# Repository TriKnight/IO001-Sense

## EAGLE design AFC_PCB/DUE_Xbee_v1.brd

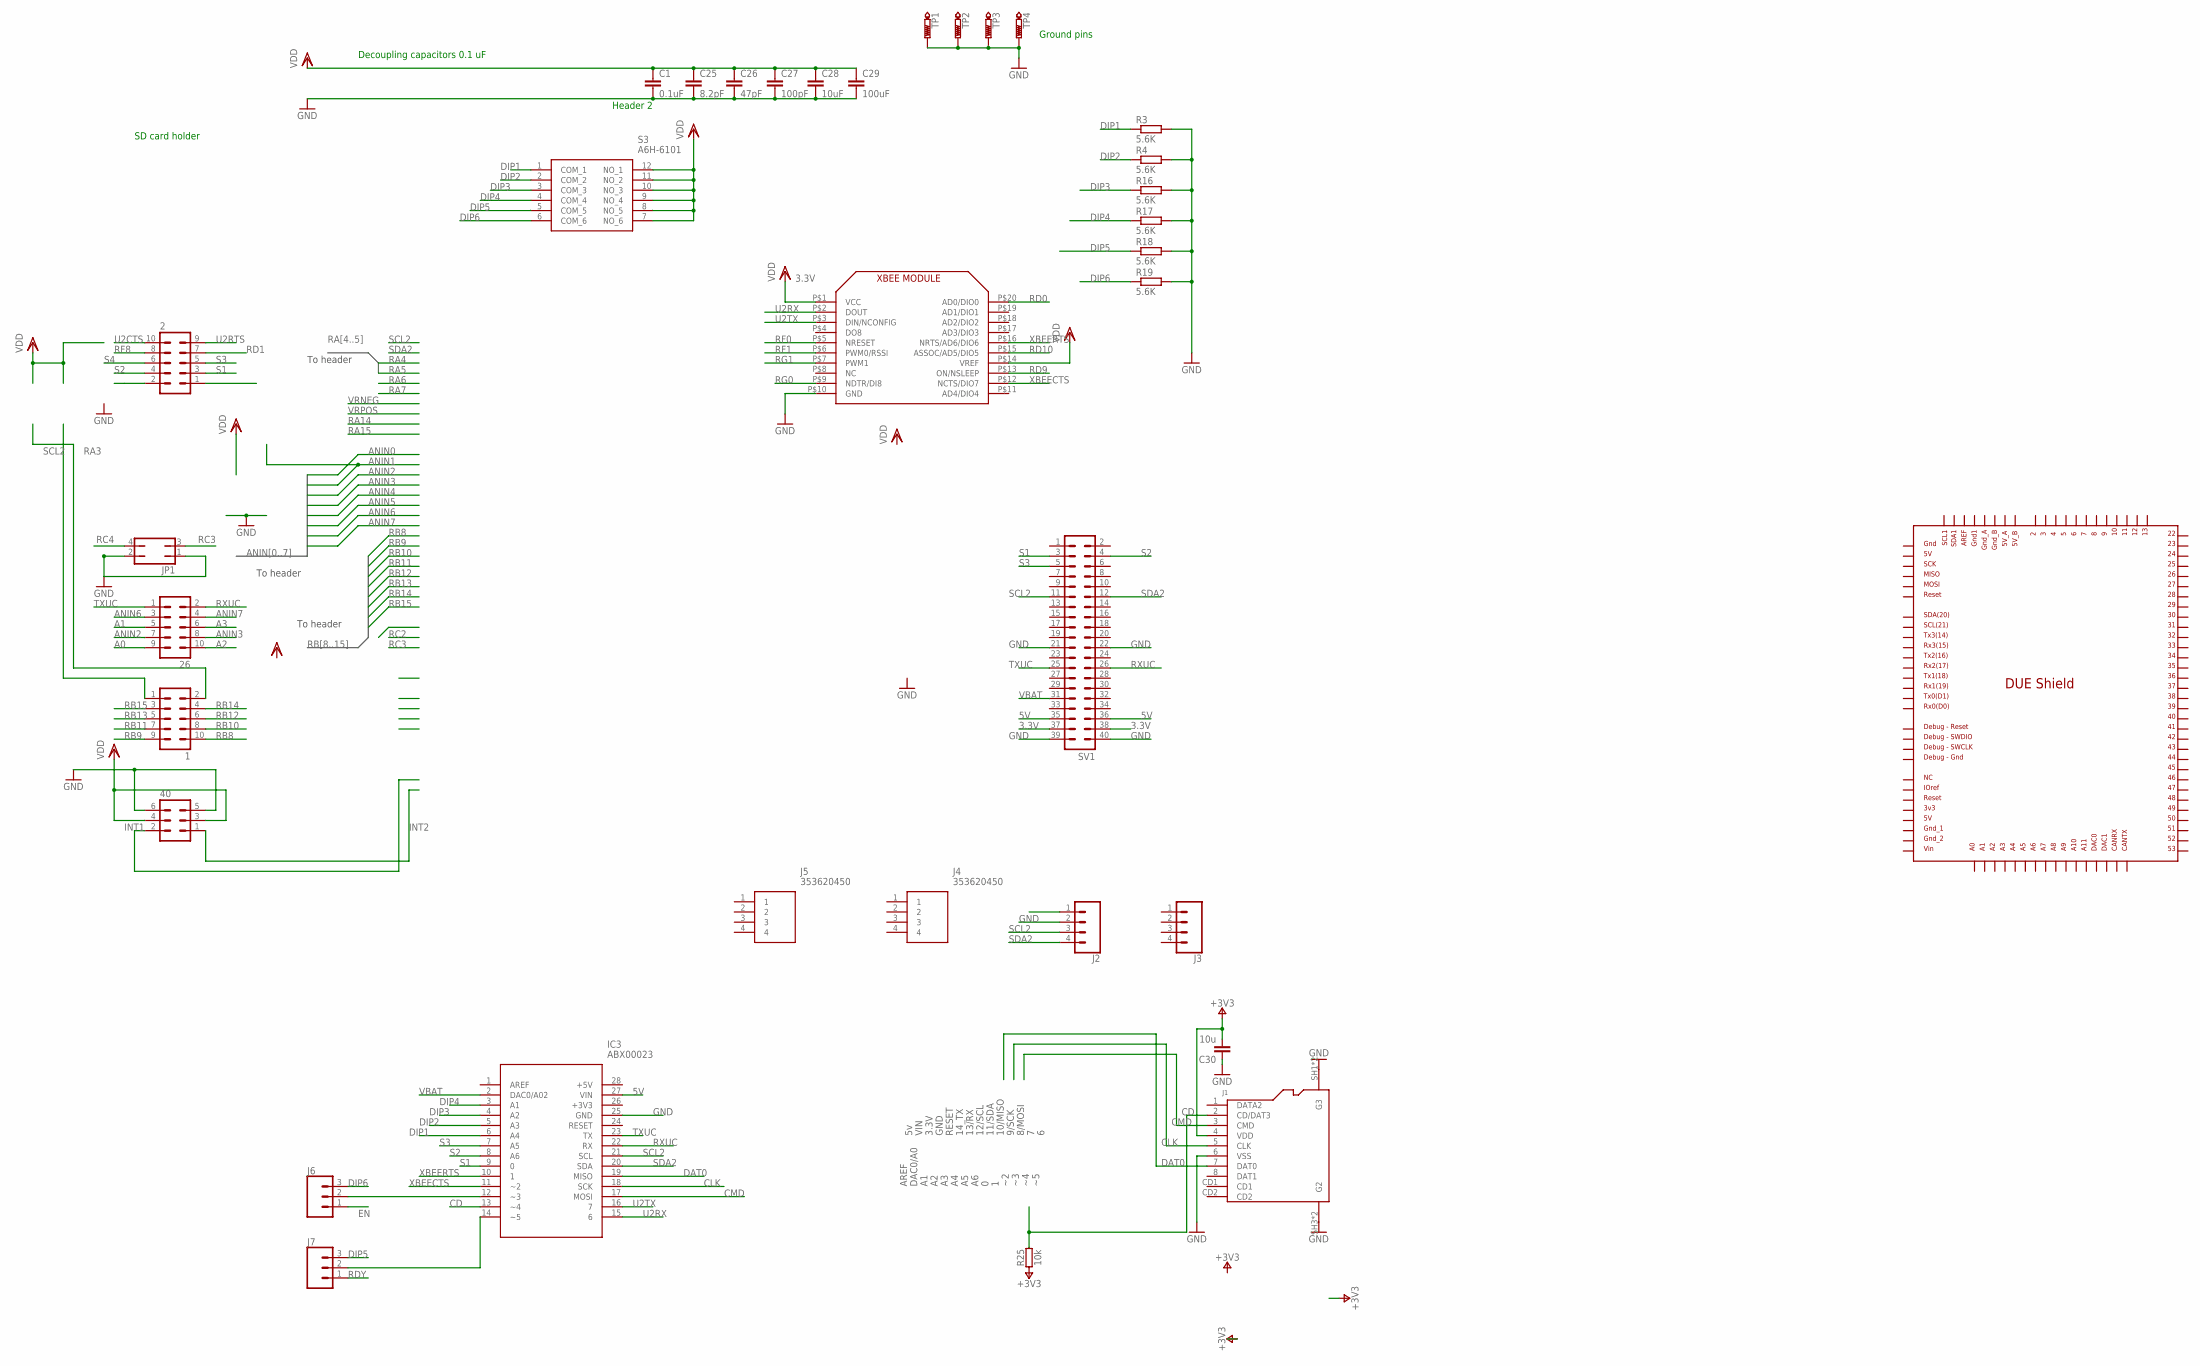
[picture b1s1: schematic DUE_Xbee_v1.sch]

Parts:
1, 2, 26: MA05-2
40: MA03-2
C1: 0.1uF; C0805K
C25: 8.2pF; C0805K
C26: 47pF; C0805K
C27: 100pF; C0805K
C28: 10uF; C0805K
C29: 100uF; C0805K
C30: 10u; 0805-R2013X50N
IC3: ABX00023
J1: AMPHENOL_114-00841-68
J2, J3: CONN_04POLAR_LOCK; MOLEX-1X4_LOCK
J4, J5: 353620450; SHDR4W50P0X200_1X4_1030X550X85
J6, J7: CONN_03LOCK; 1X03_LOCK
JP1: JP2Q
R3, R4, R16, R17, R18, R19: 5.6K; R0805
R25: 10k; 0805-R2013X50N
S3: A6H-6101; A6H6101
SV1: ML40
TP1, TP2, TP3, TP4: PTR1PAD1-13; P1-13
U$1: XBEE
U$2: DUE(NORMAL)

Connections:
3.3V: 40.3, 40.4, C1.1, C25.1, C26.1, C27.1, C28.1, C29.1, J2.1, S3.7 (NO_6), S3.8 (NO_5), S3.9 (NO_4), S3.10 (NO_3), S3.11 (NO_2), S3.12 (NO_1), SV1.37, SV1.38, U$1.P$1 (VCC), U$1.P$14 (VREF)
5V: IC3.27 (VIN), SV1.35, SV1.36
+3V3: C30.2, J1.4 (VDD), R25.1
A0: 26.9
A1: 26.5
A2: 26.10
A3: 26.6
ANIN2: 26.7
ANIN3: 26.8
ANIN6: 26.3
ANIN7: 26.4
CD: IC3.13 (~4), J1.2 (CD/DAT3), R25.2
CLK: IC3.18 (SCK), J1.5 (CLK)
CMD: IC3.17 (MOSI), J1.3 (CMD)
DAT0: IC3.19 (MISO), J1.7 (DAT0)
DIP1: IC3.6 (A4), R3.1, S3.1 (COM_1)
DIP2: IC3.5 (A3), R4.1, S3.2 (COM_2)
DIP3: IC3.4 (A2), R16.1, S3.3 (COM_3)
DIP4: IC3.3 (A1), R17.1, S3.4 (COM_4)
DIP5: J7.3, R18.1, S3.5 (COM_5)
DIP6: J6.3, R19.1, S3.6 (COM_6)
EN: J6.1
GND: 40.5, 40.6, C1.2, C25.2, C26.2, C27.2, C28.2, C29.2, C30.1, IC3.25 (GND), J1.6 (VSS), J1.SH1 (G3), J1.SH2 (G3), J1.SH3 (G2), J1.SH4 (G2), J2.2, JP1.1, JP1.2, R3.2, R4.2, R16.2, R17.2, R18.2, R19.2, SV1.21, SV1.22, SV1.39, SV1.40, TP1.1, TP2.1, TP3.1, TP4.1, U$1.P$10 (GND)
INT1: 40.2
INT2: 40.1
unnamed: IC3.12 (~3), J6.2
unnamed: IC3.14 (~5), J7.2
RA3: 1.2
RB8: 1.10
RB9: 1.9
RB10: 1.8
RB11: 1.7
RB12: 1.6
RB13: 1.5
RB14: 1.4
RB15: 1.3
RC3: JP1.3
RC4: JP1.4
RD0: U$1.P$20 (AD0/DIO0)
RD1: 2.7
RD9: U$1.P$13 (ON/NSLEEP)
RD10: U$1.P$15 (ASSOC/AD5/DIO5)
RDY: J7.1
RF0: U$1.P$5 (NRESET)
RF1: U$1.P$6 (PWM0/RSSI)
RF8: 2.8
RG0: U$1.P$9 (NDTR/DI8)
RG1: U$1.P$7 (PWM1)
RXUC: 26.2, IC3.22 (RX), SV1.26
S1: 2.3, IC3.9 (0), SV1.3
S2: 2.4, IC3.8 (A6), SV1.4
S3: 2.5, IC3.7 (A5), SV1.5
S4: 2.6
SCL2: 1.1, IC3.21 (SCL), J2.3, SV1.11
SDA2: IC3.20 (SDA), J2.4, SV1.12
TXUC: 26.1, IC3.23 (TX), SV1.25
U2CTS: 2.10
U2RTS: 2.9
U2RX: IC3.15 (6), U$1.P$2 (DOUT)
U2TX: IC3.16 (7), U$1.P$3 (DIN/NCONFIG)
VBAT: IC3.2 (DAC0/A02), SV1.31
XBEECTS: IC3.11 (~2), U$1.P$12 (NCTS/DIO7)
XBEERTS: IC3.10 (1), U$1.P$16 (NRTS/AD6/DIO6)

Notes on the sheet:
To header
SD card holder
Decoupling capacitors 0.1 uF
Header 2
Ground pins
AREF
DAC0/A0
8/MOSI
9/SCK
10/MISO
11/SDA
12/SCL
13/RX
14_TX
RESET
GND
3.3V
VIN

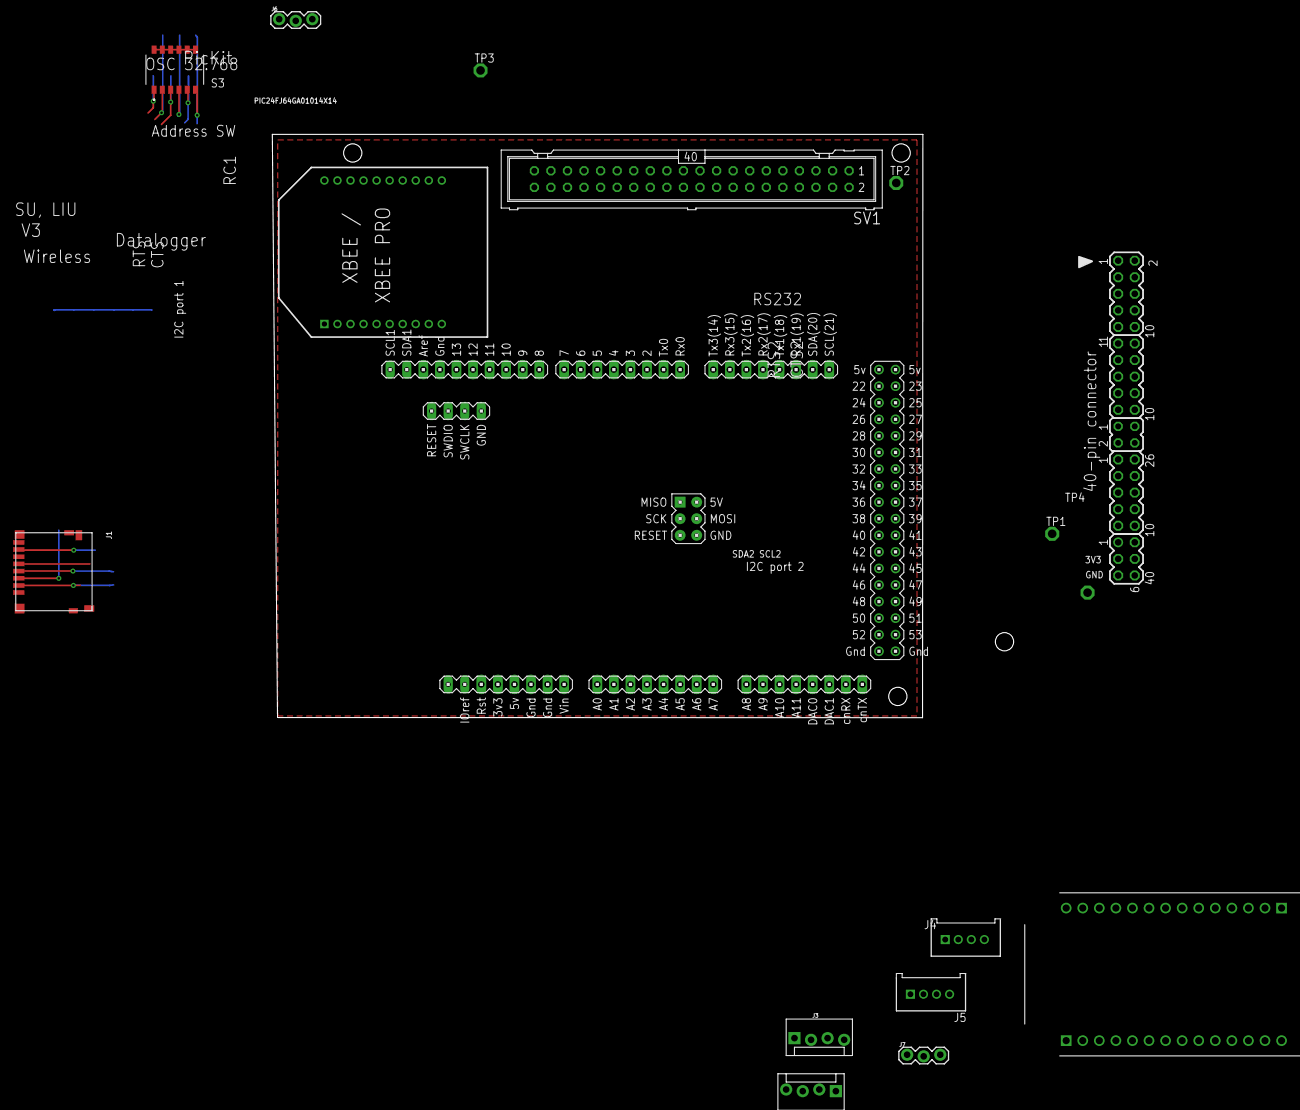
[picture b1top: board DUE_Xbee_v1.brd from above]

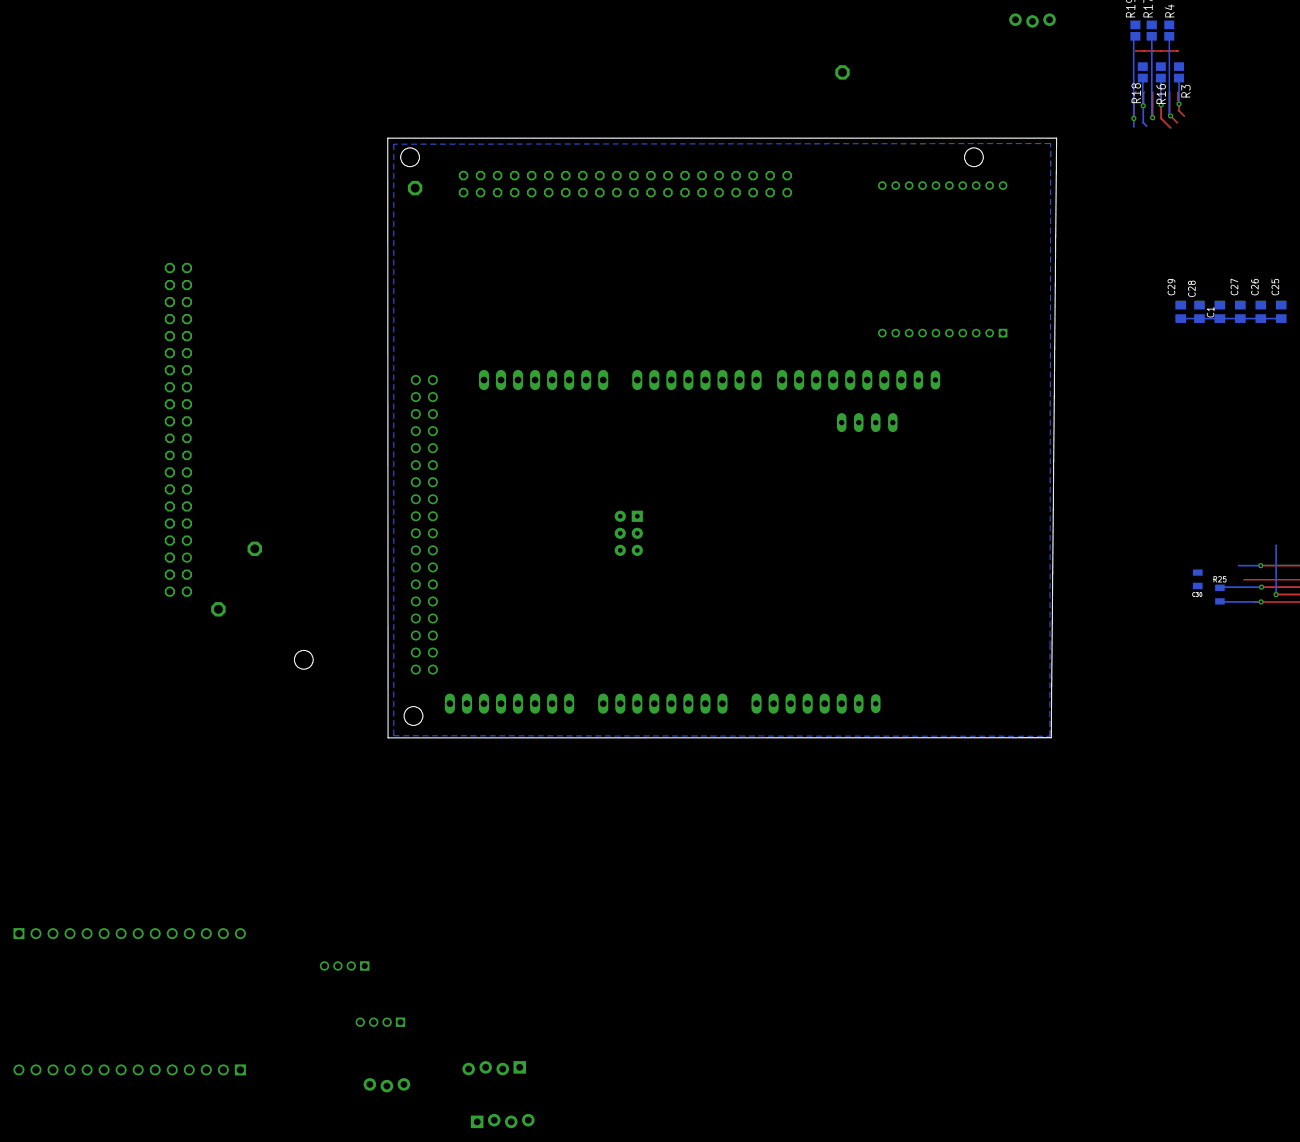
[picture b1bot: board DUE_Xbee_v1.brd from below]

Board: 2 copper layers, 99.7 x 89.4 mm, 35 parts (14 on the bottom side), 28 nets.

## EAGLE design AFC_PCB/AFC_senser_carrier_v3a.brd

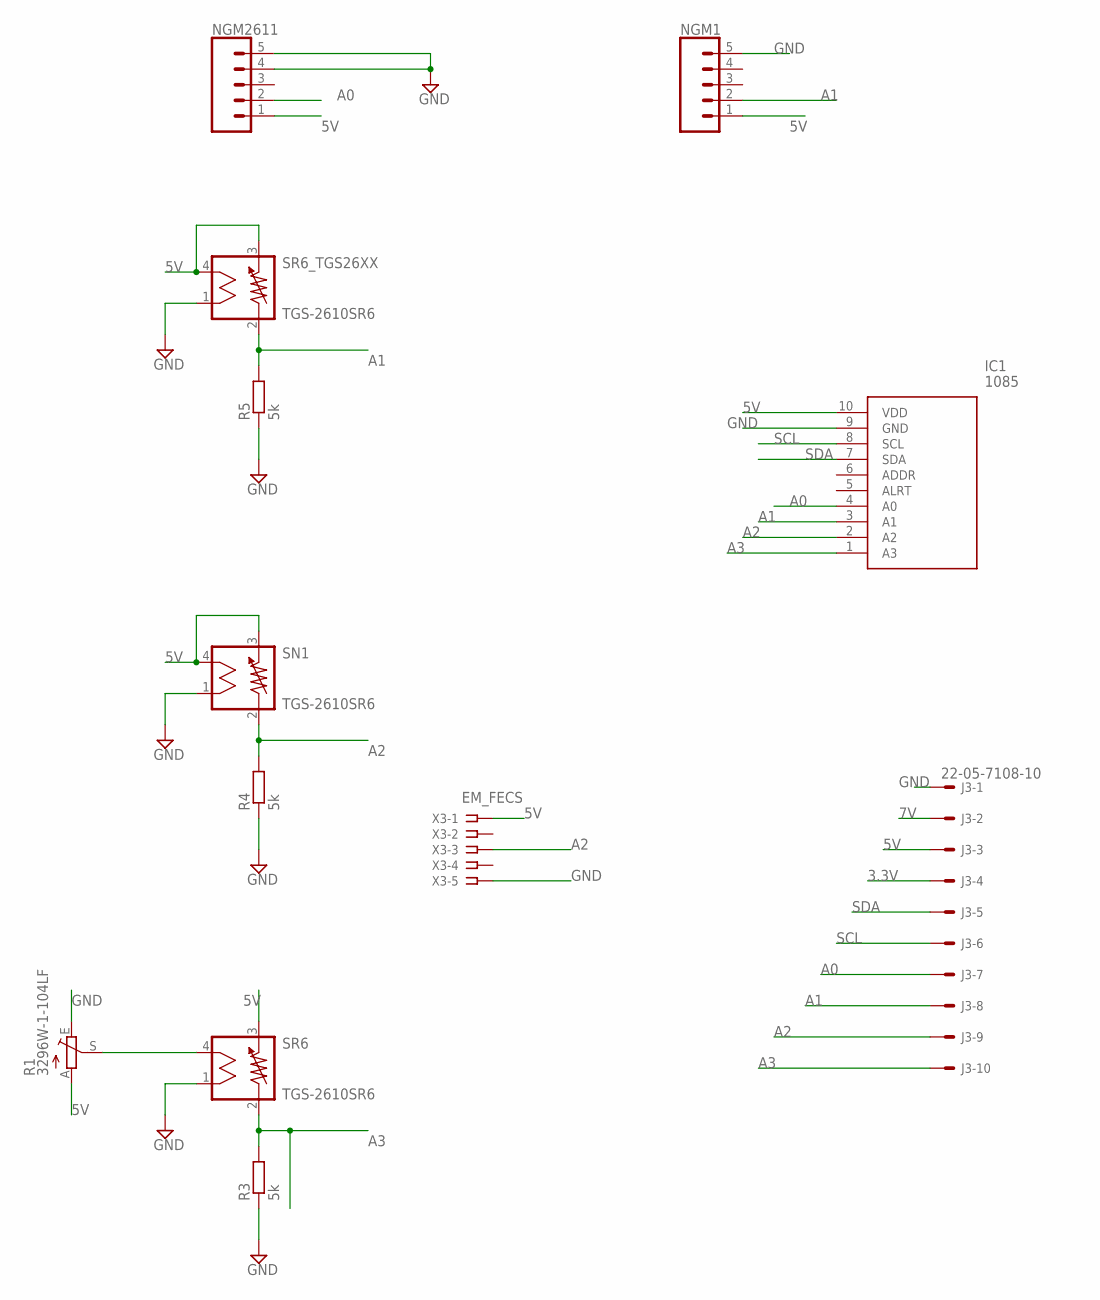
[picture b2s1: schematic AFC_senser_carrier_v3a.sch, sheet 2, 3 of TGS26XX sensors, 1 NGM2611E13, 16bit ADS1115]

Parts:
IC1: 1085
J3: 22-05-7108-10; 7395-10
NGM1, NGM2611: CONN_05LOCK; 1X05_LOCK
R1: 3296W-1-104LF; S64W
R3, R4, R5: 5k; R0805
SN1: TGS-2610SR6; SR6_TGS26XX
SR6, SR6_TGS26XX: TGS-2610SR6; SR6_TGS26XX
X3: EM_FECS; SSW-105-02-G-S

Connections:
3.3V: J3.4; also elsewhere on the board
5V: IC1.10 (VDD), J3.3, NGM1.1, NGM2611.1, R1.A, SN1.3, SN1.4, SR6.3, SR6_TGS26XX.3, SR6_TGS26XX.4, X3.1; also elsewhere on the board
7V: J3.2; also elsewhere on the board
A0: IC1.4 (A0), J3.7, NGM2611.2
A1: IC1.3 (A1), J3.8, NGM1.2, R5.2, SR6_TGS26XX.2
A2: IC1.2 (A2), J3.9, R4.2, SN1.2, X3.3
A3: IC1.1 (A3), J3.10, R3.2, SR6.2
GND: IC1.9 (GND), J3.1, NGM1.5, NGM2611.4, NGM2611.5, R1.E, R3.1, R4.1, R5.1, SN1.1, SR6.1, SR6_TGS26XX.1, X3.5; also elsewhere on the board
unnamed: R1.S, SR6.4
SCL: IC1.8 (SCL), J3.6; also elsewhere on the board
SDA: IC1.7 (SDA), J3.5; also elsewhere on the board

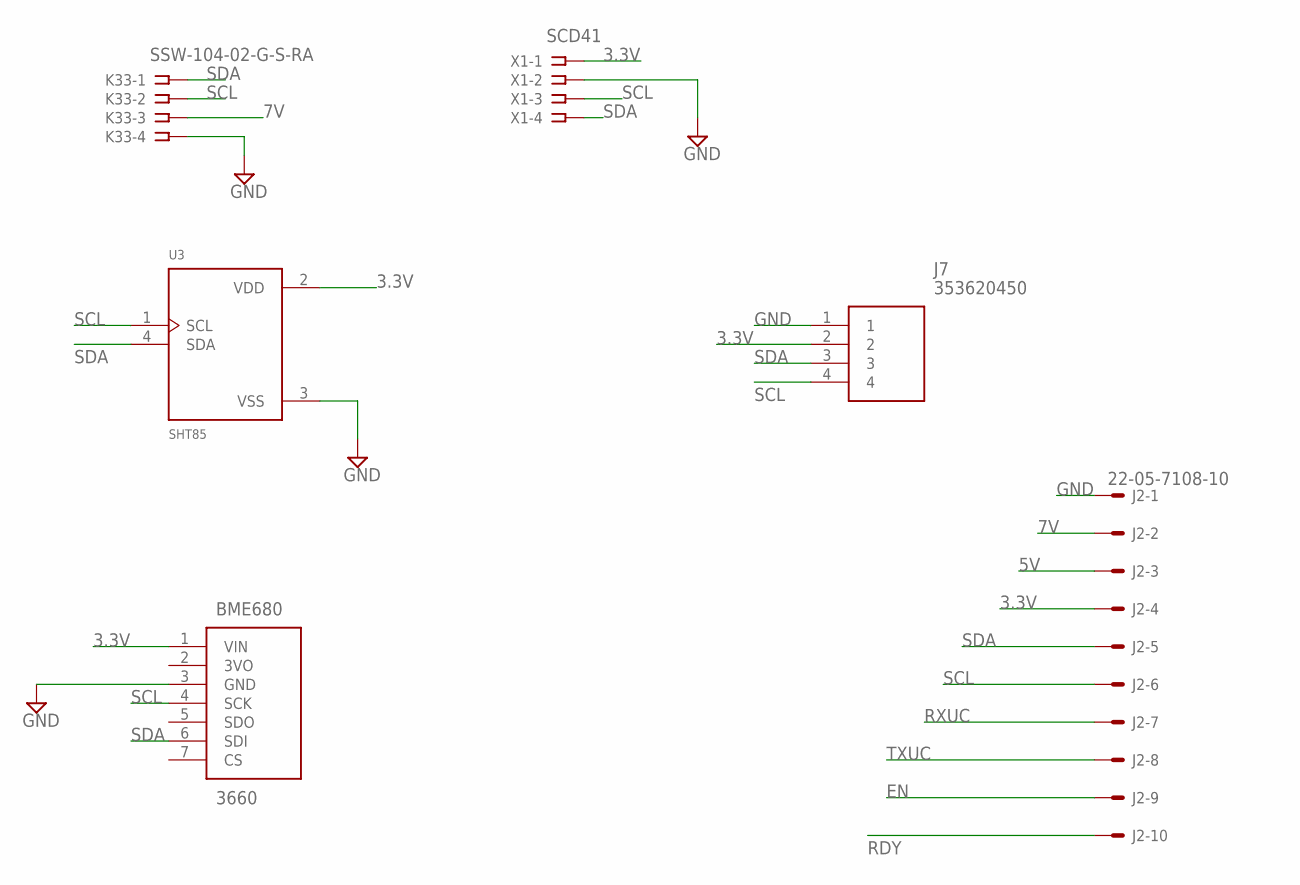
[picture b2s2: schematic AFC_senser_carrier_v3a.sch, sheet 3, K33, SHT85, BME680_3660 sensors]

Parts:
BME680: 3660
J2: 22-05-7108-10; 7395-10
J7: 353620450; SHDR4W50P0X200_1X4_1030X550X85
K33: SSW-104-02-G-S-RA
U3: SHT85; XDCR_SHT85
X1: SCD41; SSW-104-02-G-S

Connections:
3.3V: BME680.1 (VIN), J2.4, J7.2, U3.2 (VDD), X1.1; also elsewhere on the board
5V: J2.3; also elsewhere on the board
7V: J2.2, K33.3; also elsewhere on the board
EN: J2.9; also elsewhere on the board
GND: BME680.3 (GND), J2.1, J7.1, K33.4, U3.3 (VSS), X1.2; also elsewhere on the board
RDY: J2.10; also elsewhere on the board
RXUC: J2.7; also elsewhere on the board
SCL: BME680.4 (SCK), J2.6, J7.4, K33.2, U3.1 (SCL), X1.3; also elsewhere on the board
SDA: BME680.6 (SDI), J2.5, J7.3, K33.1, U3.4 (SDA), X1.4; also elsewhere on the board
TXUC: J2.8; also elsewhere on the board

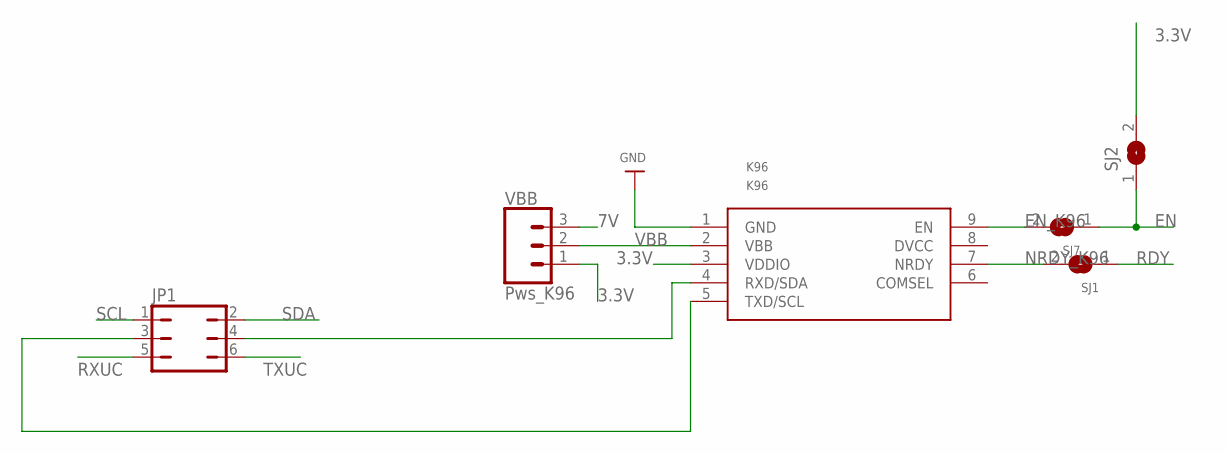
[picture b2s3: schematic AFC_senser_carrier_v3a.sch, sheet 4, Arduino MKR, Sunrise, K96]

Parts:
JP1: JP3Q
K96: K96; SENSEAIR_SUNRISE
SJ1, SJ7: SOLDERJUMPERCLOSED; SOLDERJUMPER_CLOSEDWIRE
SJ2: SJ
VBB: Pws_K96; 1X03

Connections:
3.3V: K96.3 (VDDIO), SJ2.2, VBB.1; also elsewhere on the board
7V: VBB.3; also elsewhere on the board
EN: SJ2.1, SJ7.1; also elsewhere on the board
EN_K96: K96.9 (EN), SJ7.2
GND: K96.1 (GND); also elsewhere on the board
NRDY_K96: K96.7 (NRDY), SJ1.2
RDY: SJ1.1; also elsewhere on the board
RXUC: JP1.5; also elsewhere on the board
RX_MKR: JP1.3, K96.5 (TXD/SCL)
SCL: JP1.1; also elsewhere on the board
SDA: JP1.2; also elsewhere on the board
TXUC: JP1.6; also elsewhere on the board
TX_MKR: JP1.4, K96.4 (RXD/SDA)
VBB: K96.2 (VBB), VBB.2

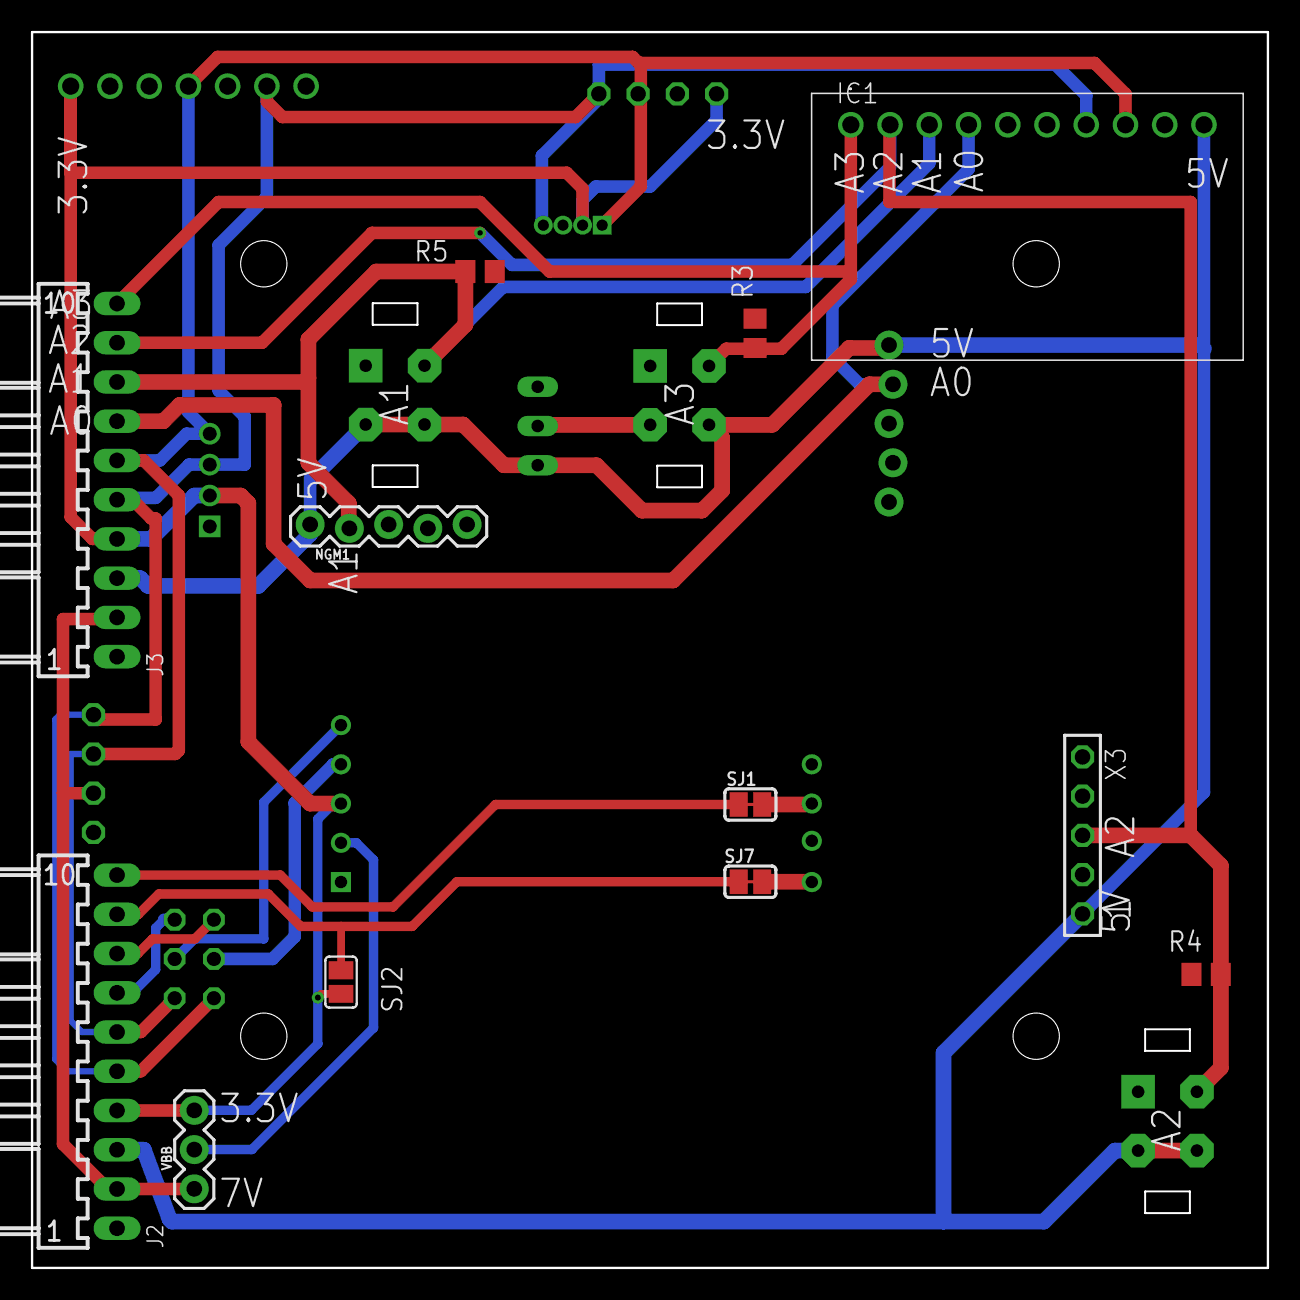
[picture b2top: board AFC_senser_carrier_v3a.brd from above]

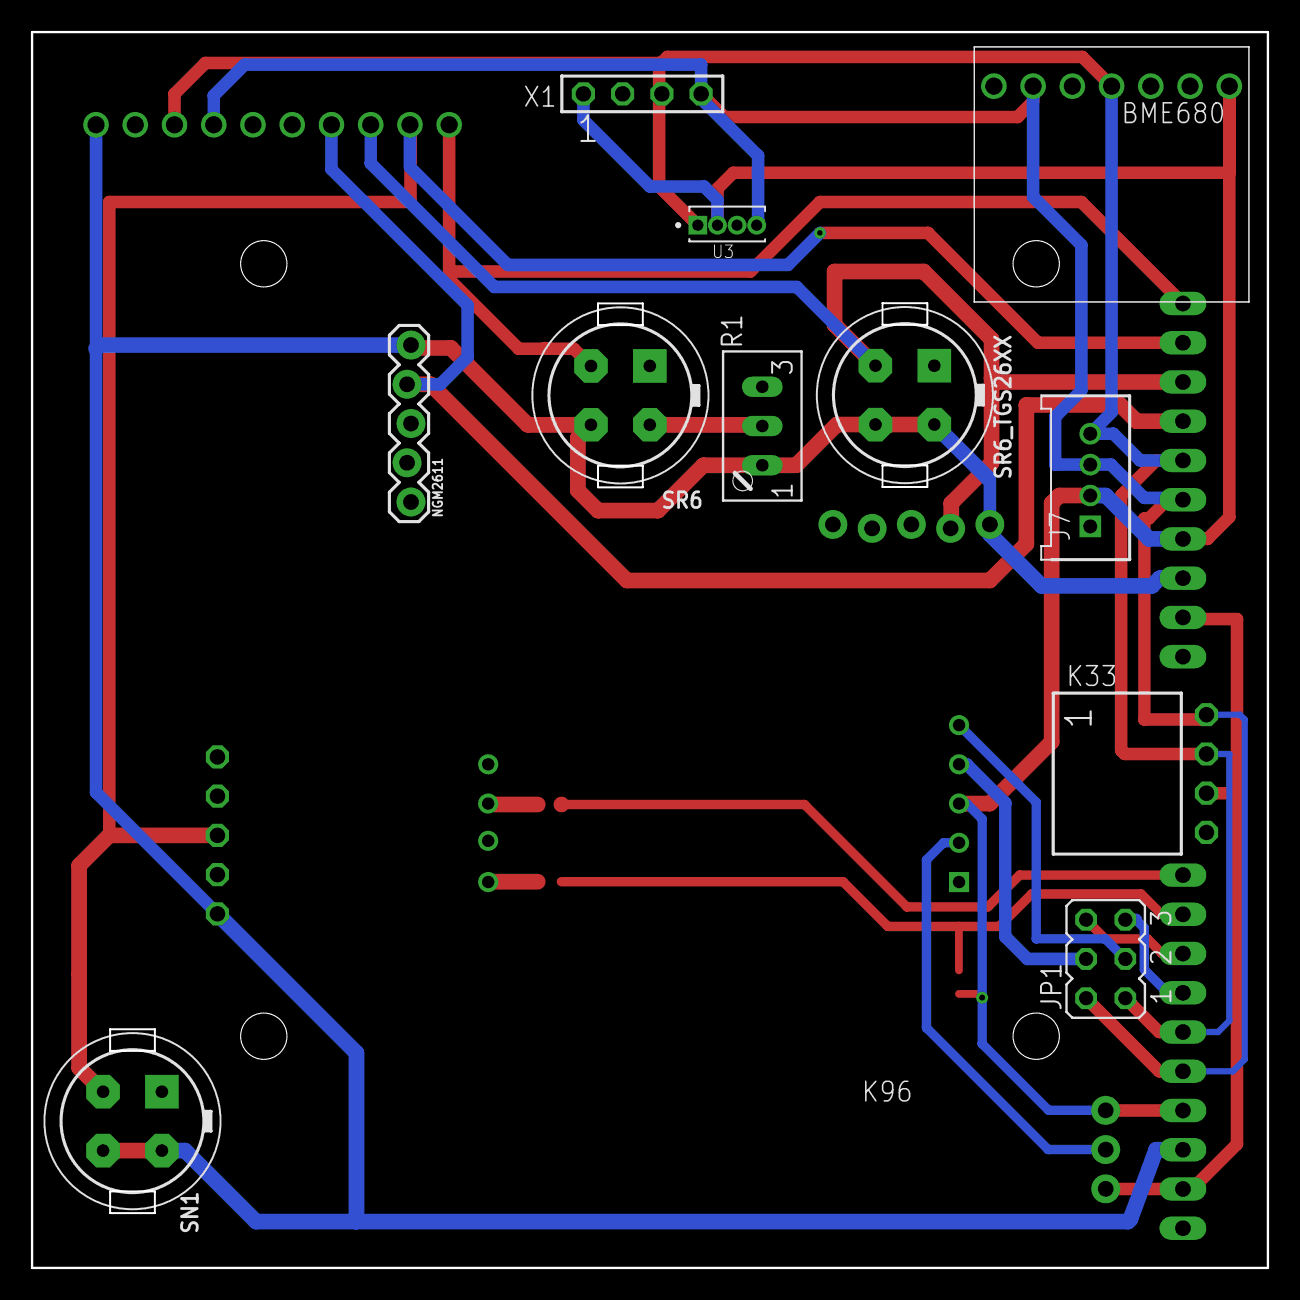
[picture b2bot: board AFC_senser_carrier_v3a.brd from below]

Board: 2 copper layers, 80.0 x 80.0 mm, 24 parts (12 on the bottom side), 20 nets.

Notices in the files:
parts and their libraries:
SparkFun-Connectors: Licensing: Creative Commons ShareAlike 4.0 International - https://creativecommons.org/licenses/by-sa/4.0
Arduino-supply: Copyright (c) 2016-2017 Arduino LLC.  All right reserved.
744770233_Eagle_WE-PD_rev20a: Copyright: Würth Elektronik
